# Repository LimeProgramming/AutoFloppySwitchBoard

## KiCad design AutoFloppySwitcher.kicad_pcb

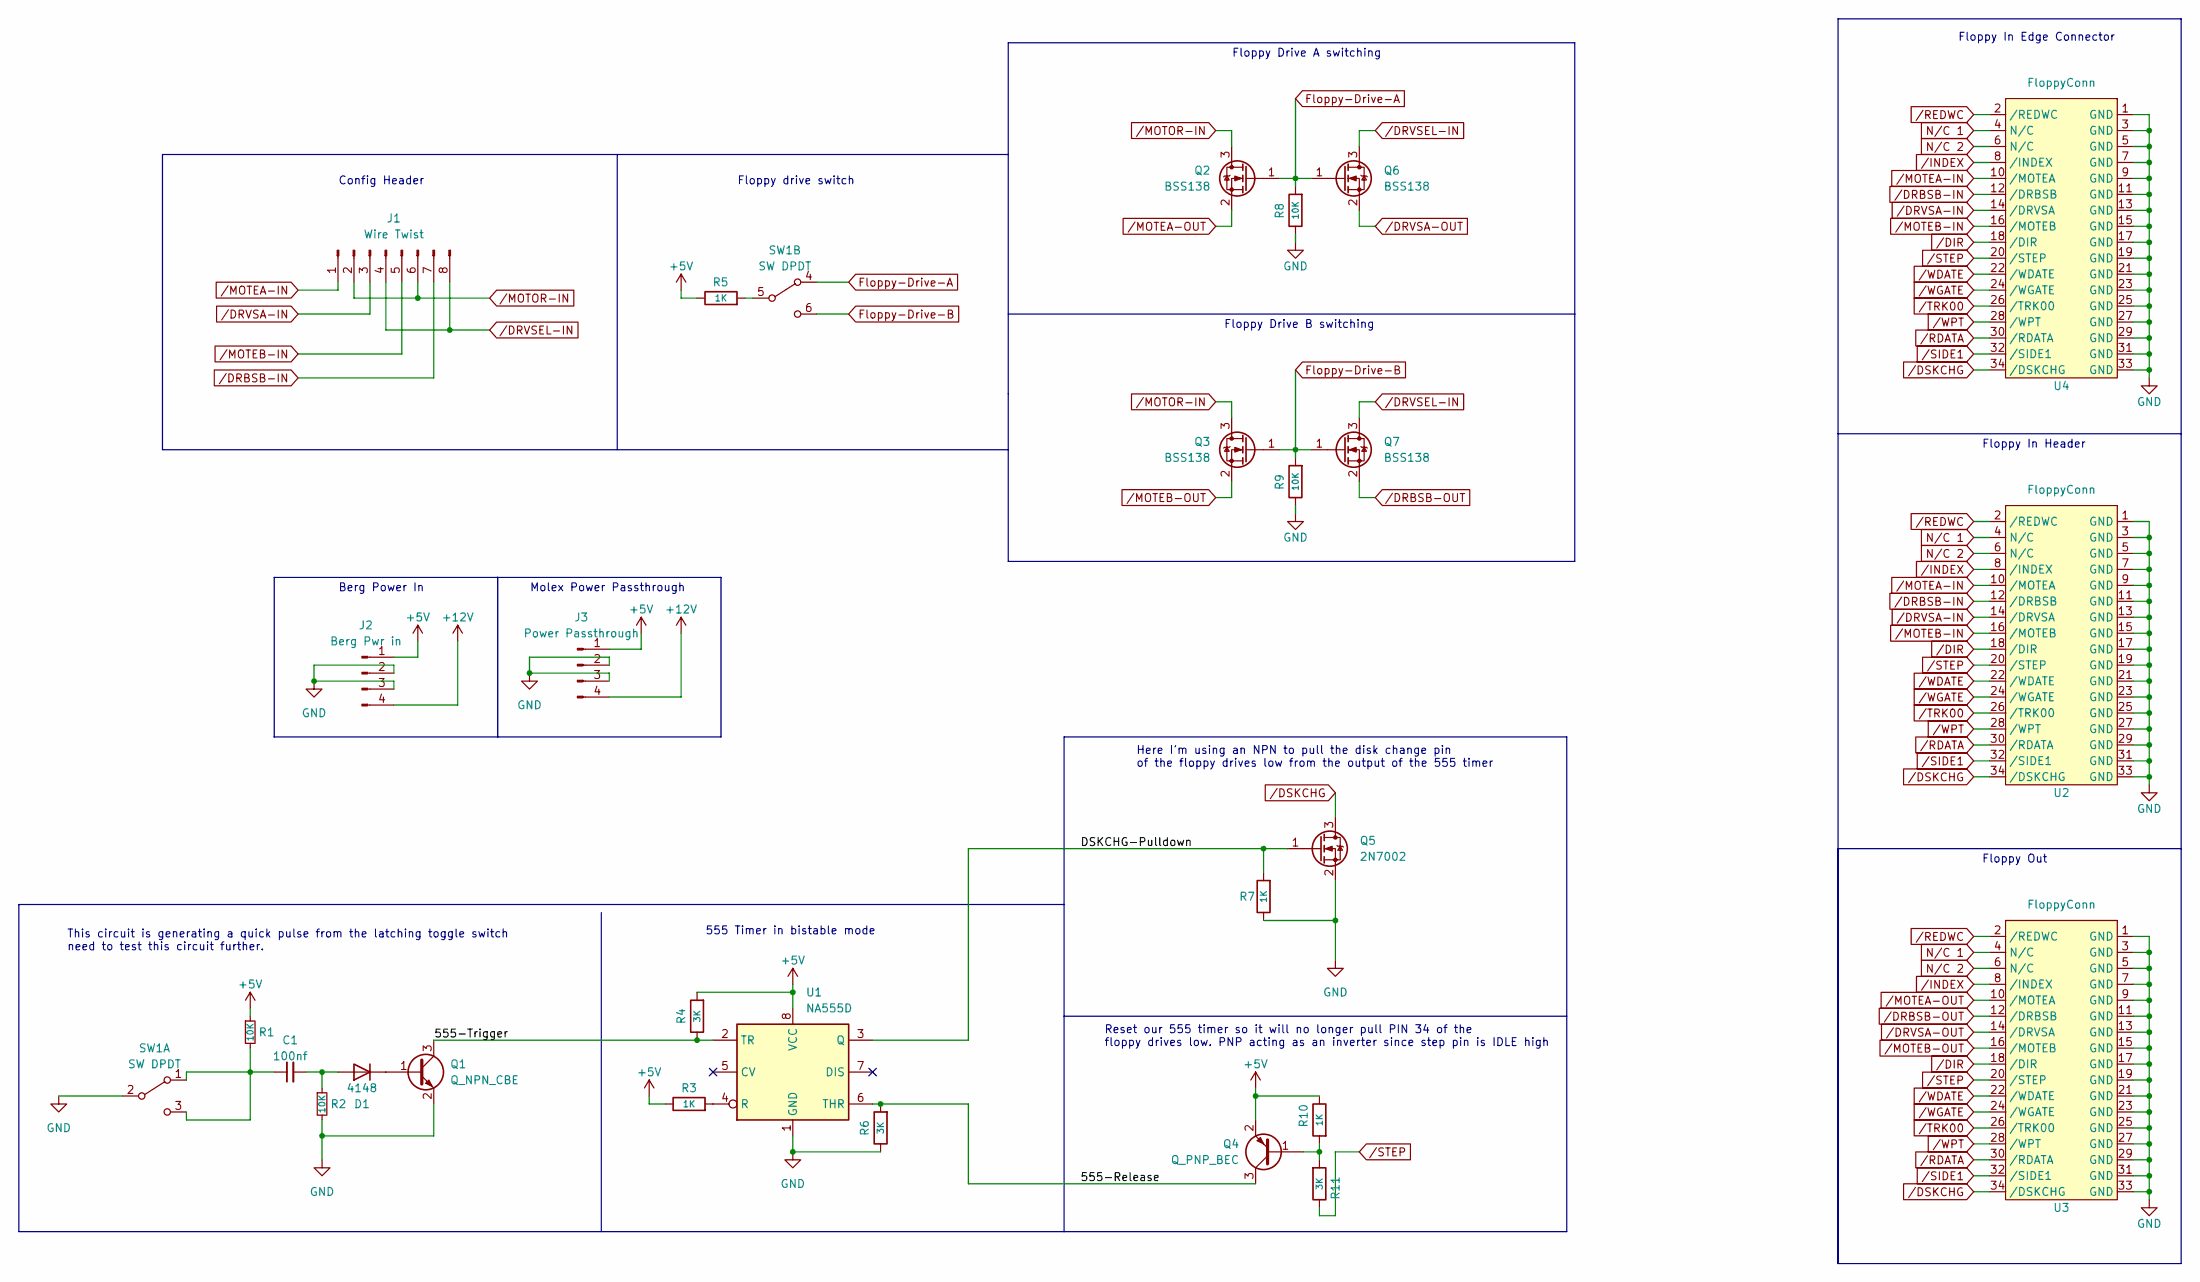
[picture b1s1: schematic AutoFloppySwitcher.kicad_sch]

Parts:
C1: 100nf; C_0805_2012Metric; JLCPCB C49678
D1: 4148; D_MiniMELF; JLCPCB C9808
J1: Wire Twist; WireTwistJumpers
J2: Berg Pwr in; berg_s
J3: Power Passthrough; Molex4pin
Q1: Q_NPN_CBE; TSOT-23_HandSoldering; JLCPCB C8512
Q2, Q3, Q6, Q7: BSS138; TSOT-23_HandSoldering; JLCPCB C8545
Q4: Q_PNP_BEC; TSOT-23_HandSoldering; JLCPCB C8326
Q5: 2N7002; TSOT-23_HandSoldering; JLCPCB C8545
R1, R2, R8, R9: 10K; R_0805_2012Metric; JLCPCB C17414
R3, R5, R7, R10: 1K; R_0805_2012Metric; JLCPCB C17513
R4, R6, R11: 3K; R_0805_2012Metric; JLCPCB C17661
SW1: SW DPDT; DPDT SW
U1: NA555D; SOIC-8_3.9x4.9mm_P1.27mm; JLCPCB C7593
U2, U3: FloppyConn; 3.5_Floppy_Header
U4: FloppyConn; FloppyCardEdge

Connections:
+5V: J2.1, J3.1, Q4.2 (E), R1.1, R3.1, R4.2, R5.1, R10.1, U1.8 (VCC)
+12V: J2.4, J3.4
/555-Release: Q4.3 (C), R6.2, U1.6 (THR)
/555-Trigger: Q1.3 (C), R4.1, U1.2 (TR)
/DSKCHG-Pulldown: Q5.1 (G), R7.2, U1.3 (Q)
Floppy-Drive-A: Q2.1 (G), Q6.1 (G), R8.2, SW1.4 (A)
Floppy-Drive-B: Q3.1 (G), Q7.1 (G), R9.2, SW1.6 (C)
GND: J2.2, J2.3, J3.2, J3.3, Q1.2 (E), Q5.2 (S), R2.2, R6.1, R7.1, R8.1, R9.1, SW1.2 (B), U1.1 (GND), U2.1 (GND), U2.3 (GND), U2.5 (GND), U2.7 (GND), U2.9 (GND), U2.11 (GND), U2.13 (GND), U2.15 (GND), U2.17 (GND), U2.19 (GND), U2.21 (GND), U2.23 (GND), U2.25 (GND), U2.27 (GND), U2.29 (GND), U2.31 (GND), U2.33 (GND), U3.1 (GND), U3.3 (GND), U3.5 (GND), U3.7 (GND), U3.9 (GND), U3.11 (GND), U3.13 (GND), U3.15 (GND), U3.17 (GND), U3.19 (GND), U3.21 (GND), U3.23 (GND), U3.25 (GND), U3.27 (GND), U3.29 (GND), U3.31 (GND), U3.33 (GND), U4.1 (GND), U4.3 (GND), U4.5 (GND), U4.7 (GND), U4.9 (GND), U4.11 (GND), U4.13 (GND), U4.15 (GND), U4.17 (GND), U4.19 (GND), U4.21 (GND), U4.23 (GND), U4.25 (GND), U4.27 (GND), U4.29 (GND), U4.31 (GND), U4.33 (GND)
unnamed: C1.1, R1.2, SW1.1 (A), SW1.3 (C)
unnamed: C1.2, D1.2 (A), R2.1
unnamed: D1.1 (K), Q1.1 (B)
unnamed: Q4.1 (B), R10.2, R11.2
unnamed: R3.2, U1.4 (R)
unnamed: R5.2, SW1.5 (B)
N/C 1: U2.4 (N/C), U3.4 (N/C), U4.4 (N/C)
N/C 2: U2.6 (N/C), U3.6 (N/C), U4.6 (N/C)
/DIR: U2.18 (/DIR), U3.18 (/DIR), U4.18 (/DIR)
/DRBSB-IN: J1.7, U2.12 (/DRBSB), U4.12 (/DRBSB)
/DRBSB-OUT: Q7.2 (S), U3.12 (/DRBSB)
/DRVSA-IN: J1.3, U2.14 (/DRVSA), U4.14 (/DRVSA)
/DRVSA-OUT: Q6.2 (S), U3.14 (/DRVSA)
/DRVSEL-IN: J1.4, J1.8, Q6.3 (D), Q7.3 (D)
/DSKCHG: Q5.3 (D), U2.34 (/DSKCHG), U3.34 (/DSKCHG), U4.34 (/DSKCHG)
/INDEX: U2.8 (/INDEX), U3.8 (/INDEX), U4.8 (/INDEX)
/MOTEA-IN: J1.1, U2.10 (/MOTEA), U4.10 (/MOTEA)
/MOTEA-OUT: Q2.2 (S), U3.10 (/MOTEA)
/MOTEB-IN: J1.5, U2.16 (/MOTEB), U4.16 (/MOTEB)
/MOTEB-OUT: Q3.2 (S), U3.16 (/MOTEB)
/MOTOR-IN: J1.2, J1.6, Q2.3 (D), Q3.3 (D)
/RDATA: U2.30 (/RDATA), U3.30 (/RDATA), U4.30 (/RDATA)
/REDWC: U2.2 (/REDWC), U3.2 (/REDWC), U4.2 (/REDWC)
/SIDE1: U2.32 (/SIDE1), U3.32 (/SIDE1), U4.32 (/SIDE1)
/STEP: R11.1, U2.20 (/STEP), U3.20 (/STEP), U4.20 (/STEP)
/TRK00: U2.26 (/TRK00), U3.26 (/TRK00), U4.26 (/TRK00)
/WDATE: U2.22 (/WDATE), U3.22 (/WDATE), U4.22 (/WDATE)
/WGATE: U2.24 (/WGATE), U3.24 (/WGATE), U4.24 (/WGATE)
/WPT: U2.28 (/WPT), U3.28 (/WPT), U4.28 (/WPT)

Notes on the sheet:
555 Timer in bistable mode
Floppy Out
Reset our 555 timer so it will no longer pull PIN 34 of the floppy drives low. PNP acting as an inverter since step pin is IDLE high
Floppy Drive A switching
This circuit is generating a quick pulse from the latching toggle switch need to test this circuit further.
Berg Power In
Config Header
Molex Power Passthrough
Here I'm using an NPN to pull the disk change pin of the floppy drives low from the output of the 555 timer
Floppy In Header
Floppy Drive B switching
Floppy In Edge Connector
Floppy drive switch

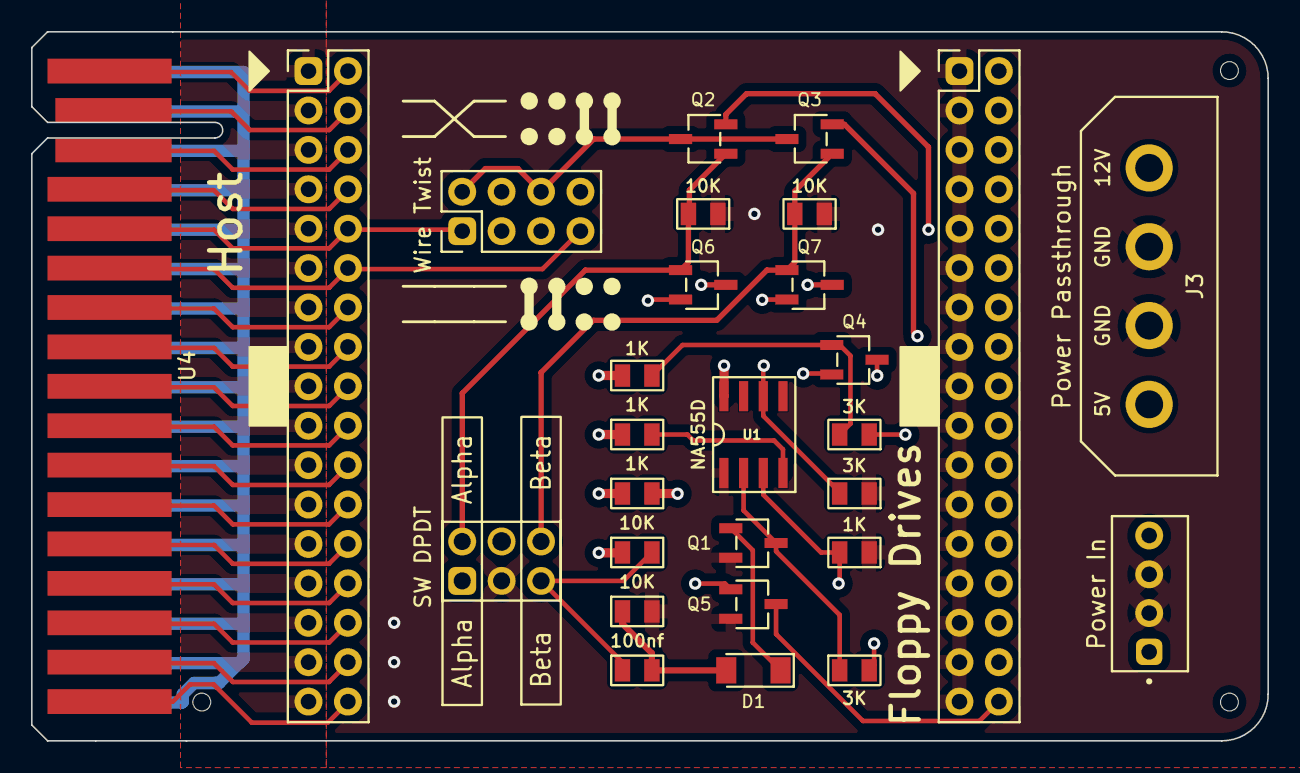
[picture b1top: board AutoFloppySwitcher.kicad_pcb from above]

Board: 4 copper layers, 79.7 x 45.7 mm, 28 parts (0 on the bottom side), 37 nets.

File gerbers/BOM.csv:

Designator,Footprint,Quantity,Value,LCSC Part #,JLCPCB
C1,C_0805_2012Metric,1,100nf,,C49678
R11,R_0805_2012Metric,1,3K,,C17661
R10,R_0805_2012Metric,1,1K,,C17513
R8,R_0805_2012Metric,1,10K,,C17414
Q2,TSOT-23_HandSoldering,1,BSS138,,C8545
Q6,TSOT-23_HandSoldering,1,BSS138,,C8545
R3,R_0805_2012Metric,1,1K,,C17513
R7,R_0805_2012Metric,1,1K,,C17513
D1,D_MiniMELF,1,4148,,C9808
R4,R_0805_2012Metric,1,3K,,C17661
Q5,TSOT-23_HandSoldering,1,2N7002,,C8545
Q3,TSOT-23_HandSoldering,1,BSS138,,C8545
Q7,TSOT-23_HandSoldering,1,BSS138,,C8545
R6,R_0805_2012Metric,1,3K,,C17661
R9,R_0805_2012Metric,1,10K,,C17414
R1,R_0805_2012Metric,1,10K,,C17414
U1,SOIC-8_3.9x4.9mm_P1.27mm,1,NA555D,,C7593
R2,R_0805_2012Metric,1,10K,,C17414
Q1,TSOT-23_HandSoldering,1,Q_NPN_CBE,,C8512
Q4,TSOT-23_HandSoldering,1,Q_PNP_BEC,,C8326
R5,R_0805_2012Metric,1,1K,,C17513

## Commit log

2023-02-06 upload
2023-02-06 gerbers
2023-02-06 added image
